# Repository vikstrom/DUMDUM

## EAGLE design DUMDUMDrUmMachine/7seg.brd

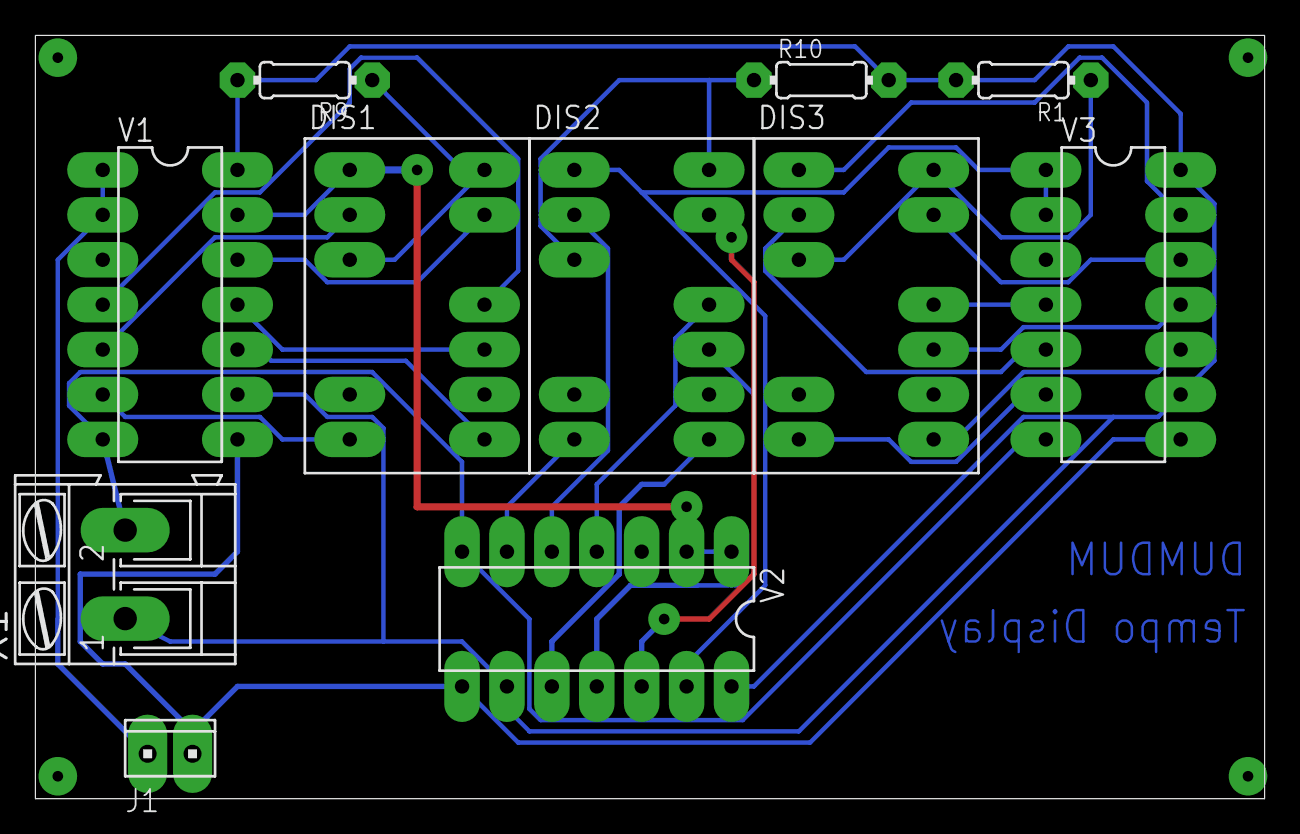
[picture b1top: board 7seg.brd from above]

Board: 2 copper layers, 69.5 x 43.2 mm, 11 parts (0 on the bottom side), 28 nets.

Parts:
DIS1, DIS2, DIS3: HD-E100; HDSP-I
J1: 10X02MTA
R1, R9, R10: 100; 0204/7
V1, V2, V3: 74164N; DIL14
X1: AK300/2

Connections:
+5V: R1.2, R9.2, R10.2, V1.9, V1.14, V2.9, V2.14, V3.9, V3.14, X1.1
CLOCK_PIN_164: J1.1, V1.8, V2.8, V3.8
DATA_PIN_164: J1.2, V1.1, V1.2
GND: V1.7, V2.7, V3.7, X1.2
unnamed: DIS2.1, V2.13, V3.1, V3.2
unnamed: DIS1.11, V1.4
unnamed: DIS1.2, V1.5
unnamed: DIS1.7, V1.6
unnamed: DIS1.8, V1.10
unnamed: DIS1.10, V1.11
unnamed: DIS1.13, V1.12
unnamed: DIS3.11, V3.4
unnamed: DIS1.1, V1.13, V2.1, V2.2
unnamed: DIS2.11, V2.4
unnamed: DIS2.2, V2.5
unnamed: DIS2.7, V2.6
unnamed: DIS2.8, V2.10
unnamed: DIS2.10, V2.11
unnamed: DIS2.13, V2.12
unnamed: DIS1.3, DIS1.14, R9.1
unnamed: DIS3.2, V3.5
unnamed: DIS3.7, V3.6
unnamed: DIS3.8, V3.10
unnamed: DIS3.10, V3.11
unnamed: DIS3.13, V3.12
unnamed: DIS3.1, V3.13
unnamed: DIS2.3, DIS2.14, R10.1
unnamed: DIS3.3, DIS3.14, R1.1

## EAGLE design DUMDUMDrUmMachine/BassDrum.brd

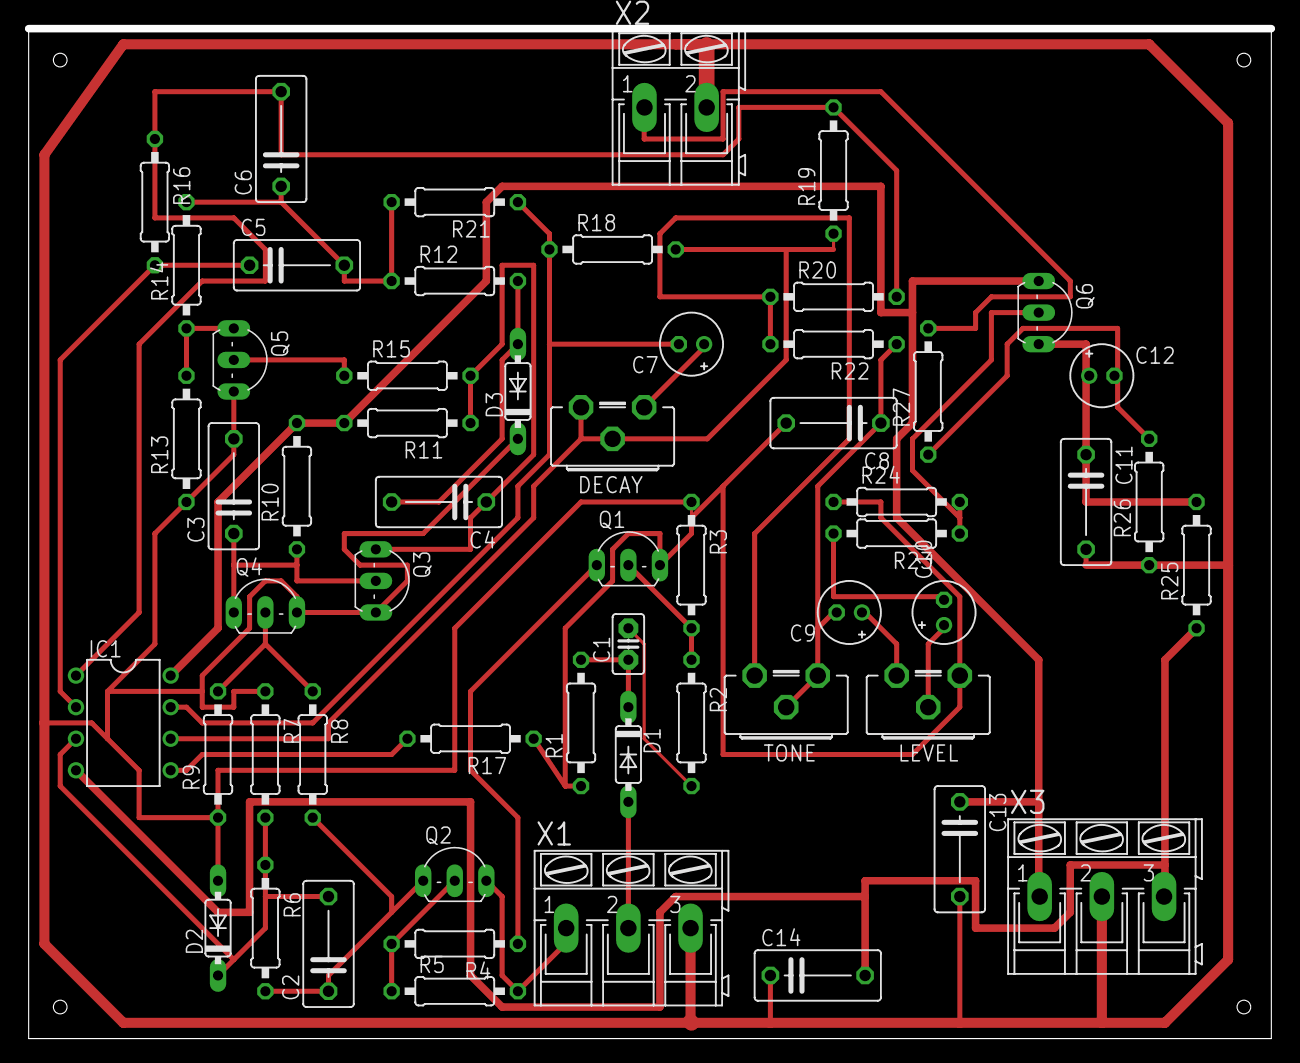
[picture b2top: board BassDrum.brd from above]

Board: 2 copper layers, 100.0 x 81.3 mm, 57 parts (0 on the bottom side), 34 nets.

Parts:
C1: 0.1; C2.5-2
C2, C5, C6: 15n; C075-042X103
C3, C8, C13, C14: 100n; C075-042X103
C4: 33n; C075-042X103
C7: 33u/6.3V; E2-5
C9, C10: 0.47u/50V; E2-5
C11: 220p; C075-042X103
C12: 1u/50V; E2-5
D1, D2, D3: 1N4148DO35-7; DO35-7
DECAY: 500k; CA9H
IC1: TL072P; DIL08
LEVEL: 10k; CA9H
Q1, Q3, Q4, Q5, Q6: BC546A; TO92-EBC
Q2: BC556A; TO92-EBC
R1, R6, R15, R24, R26: 100k; 0207/10
R2, R11, R17: 22k; 0207/10
R3, R4, R22: 10k; 0207/10
R5, R7: 4.7k; 0207/10
R8: 8.2k; 0207/10
R9: 2.7k; 0207/10
R10, R12, R16: 1M; 0207/10
R13, R18, R19: 47k; 0207/10
R14: 6.9k; 0207/10
R20: 220; 0207/10
R21: 470k; 0207/10
R23: 82k; 0207/10
R25: 5.9k; 0207/10
R27: 1k; 0207/10
TONE: 10k; CA9H
X1: ACC+TRIG; AK300/3
X2: OUT; AK300/2
X3: SUPPLY; AK300/3

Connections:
+15V: C13.1, IC1.8, Q6.C, R10.2, R11.2, X3.1
-15V: C14.2, IC1.4, R25.1, X3.3
GND: C3.2, C8.2, C11.2, C13.2, C14.1, D2.A, D3.C, LEVEL.A, Q1.E, Q3.E, Q4.E, Q5.E, R1.1, R3.1, R7.1, R9.1, R13.1, R17.1, R24.1, R26.1, X1.3, X2.2, X3.2
unnamed: Q2.E, R5.2, X1.1
unnamed: C1.1, D1.C, R1.2
unnamed: C1.2, R2.2
unnamed: Q1.B, R2.1, R3.2
unnamed: DECAY.E, DECAY.S, IC1.6, R18.2, R19.1
unnamed: Q1.C, R4.1
unnamed: Q2.B, R4.2, R5.1
unnamed: D1.A, X1.2
unnamed: C2.1, Q2.C, R6.2, R8.2
unnamed: C2.2, D2.C, IC1.3, R6.1, R7.2
unnamed: Q4.B, R8.1, R9.2
unnamed: C4.2, D3.A, R12.2
unnamed: C3.1, Q3.B, Q4.C, R10.1
unnamed: C4.1, Q3.C, R11.1, R15.2
unnamed: Q5.B, R15.1
unnamed: Q5.C, R13.2, R14.1
unnamed: IC1.5, R17.2
unnamed: C5.1, IC1.2, R16.2
unnamed: C6.2, IC1.1, R16.1, R19.2, R20.2
unnamed: C7.-, IC1.7, R18.1, R21.1
unnamed: C7.+, DECAY.A
unnamed: R20.1, R22.2, TONE.E
unnamed: C8.1, C9.-, R22.1, TONE.A, TONE.S
unnamed: C10.+, LEVEL.S
unnamed: C10.-, R23.2
unnamed: Q6.B, R23.1, R24.2
unnamed: C9.+, LEVEL.E
unnamed: C11.1, C12.+, Q6.E, R25.2
unnamed: C12.-, R26.2, R27.1
unnamed: R27.2, X2.1
unnamed: C5.2, C6.1, R12.1, R14.2, R21.2

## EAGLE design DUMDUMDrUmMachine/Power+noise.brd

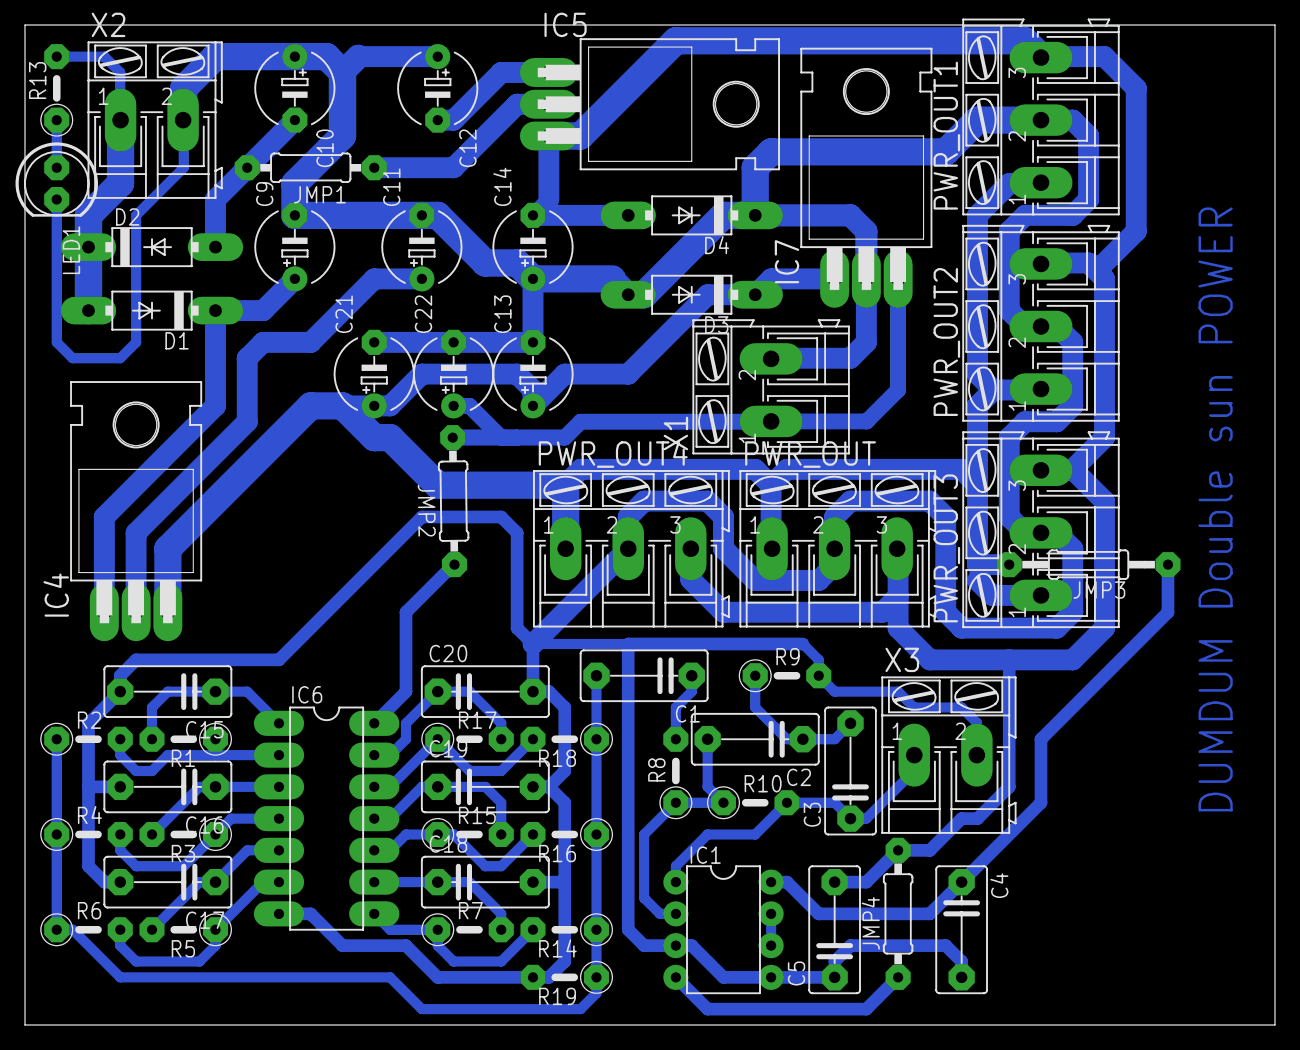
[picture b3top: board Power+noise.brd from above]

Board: 2 copper layers, 100.0 x 80.0 mm, 58 parts (0 on the bottom side), 32 nets.

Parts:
C1: 1n; C075-042X103
C2, C3: 3.3n; C075-042X103
C4, C5: 0.1u; C075-042X103
C9, C10: 470u; E5-6
C11, C12: 25u; E5-6
C13, C14, C21, C22: 1u; E5-6
C15: 22n; C075-042X103
C16, C17, C20: 19n; C075-042X103
C18, C19: 10n; C075-042X103
D1, D2, D3, D4: BYT01; F126-10
IC1: TL072P; DIL08
IC4: 7815T; TO220H
IC5: TO220H
IC6: 4584N; DIL14
IC7: 7805T; TO220H
JMP1, JMP2, JMP4: 0; 0207/10
JMP3: 0; 0207/12
LED1: LED5MM
PWR_OUT, PWR_OUT1, PWR_OUT2, PWR_OUT3, PWR_OUT4: +15V, GND, -15V; AK300/3
R1: 300k; 0207/5V
R2, R4, R6, R14, R16, R18, R19: 120k; 0207/5V
R3: 270k; 0207/5V
R5: 220k; 0207/5V
R7: 680k; 0207/5V
R8: 22k; 0207/5V
R9: 580; 0207/5V
R10: 82k; 0207/5V
R13: 1.2k; 0207/5V
R15: 560k; 0207/5V
R17: 560; 0207/5V
X1: 5 VDC; AK300/2
X2: 15 VAC; AK300/2
X3: NOISE_OUT; AK300/2

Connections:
+5V: C22.+, IC7.3, JMP2.2, X1.1
+15V: C13.+, C21.+, D3.C, IC4.3, IC7.1, JMP3.2, PWR_OUT.1, PWR_OUT1.1, PWR_OUT2.1, PWR_OUT3.1, PWR_OUT4.1
-15V: C5.2, C14.-, D4.A, IC5.3, JMP4.2, PWR_OUT.3, PWR_OUT1.3, PWR_OUT2.3, PWR_OUT3.3, PWR_OUT4.3
GND: C4.2, C5.1, C9.-, C10.+, C11.-, C12.+, C13.-, C14.+, C15.2, C16.2, C17.2, C18.2, C19.2, C20.2, C21.-, C22.-, D3.A, D4.C, IC1.3, IC1.5, IC6.7, IC7.2, LED1.K, PWR_OUT.2, PWR_OUT1.2, PWR_OUT2.2, PWR_OUT3.2, PWR_OUT4.2, R9.2, R19.2, X1.2, X2.2, X3.2
unnamed: C1.2, R2.1, R4.1, R6.1, R14.1, R16.1, R18.1, R19.1
unnamed: IC6.12, R17.1, R18.2
unnamed: IC6.10, R15.1, R16.2
unnamed: IC6.8, R7.1, R14.2
unnamed: IC6.6, R5.1, R6.2
unnamed: IC6.4, R3.1, R4.2
unnamed: IC6.2, R1.1, R2.2
unnamed: C20.1, IC6.13, R17.2
unnamed: C19.1, IC6.11, R15.2
unnamed: C10.-, D2.A, JMP1.2
unnamed: C1.1, R8.2
unnamed: C2.2, IC1.2, R8.1, R10.1
unnamed: C3.1, IC1.1, R10.2, X3.1
unnamed: C2.1, C3.2, R9.1
unnamed: C18.1, IC6.9, R7.2
unnamed: C17.1, IC6.5, R5.2
unnamed: C16.1, IC6.3, R3.2
unnamed: C15.1, IC6.1, R1.2
unnamed: D1.A, D2.C, R13.2, X2.1
unnamed: LED1.A, R13.1
unnamed: IC1.6, IC1.7
unnamed: C9.+, D1.C, IC4.1
unnamed: IC5.2, JMP1.1
unnamed: C11.+, IC4.2
unnamed: IC6.14, JMP2.1
unnamed: C12.-, IC5.1
unnamed: IC1.4, JMP4.1
unnamed: C4.1, IC1.8, JMP3.1
